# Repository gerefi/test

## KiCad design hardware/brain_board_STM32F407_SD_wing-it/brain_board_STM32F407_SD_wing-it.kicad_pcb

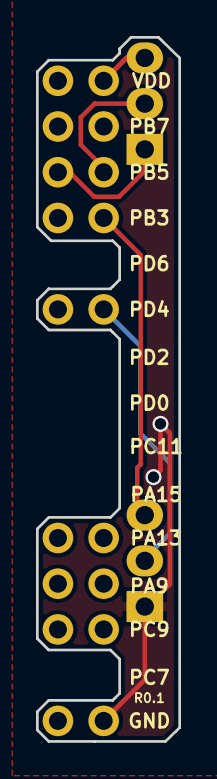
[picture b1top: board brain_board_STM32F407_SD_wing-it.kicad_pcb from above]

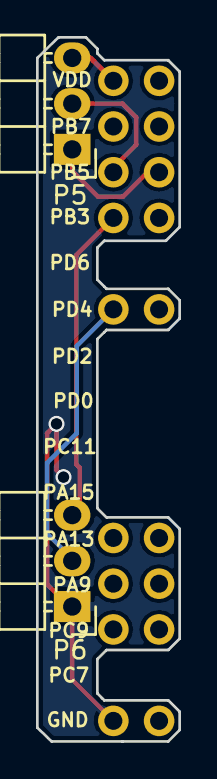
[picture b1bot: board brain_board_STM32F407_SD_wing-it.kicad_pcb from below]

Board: 2 copper layers, 7.9 x 39.1 mm, 8 parts (2 on the bottom side), 6 nets.

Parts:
P1: CONN_02X04; Pin_Header_Straight_2x04_Pitch2.54mm
P2: CONN_02X03; Pin_Header_Straight_2x03_Pitch2.54mm
P5, P6: CONN_01X03; Pin_Header_Angled_1x03
P7, P8, P11, P12: CONN_01X01; Pin_Header_Straight_1x01_Pitch2.54mm

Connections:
/PB3: P1.8, P6.3
/PB4: P1.5, P5.1
/PB5: P1.6, P5.2
/PD4: P6.2, P7.1
/VDD: P1.2, P5.3
GND: P6.1, P8.1

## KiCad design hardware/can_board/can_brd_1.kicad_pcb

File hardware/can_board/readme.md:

CAN using SN65HVD230

[Forum thread](http://gerefi.com/forum/viewtopic.php?f=4&t=353)

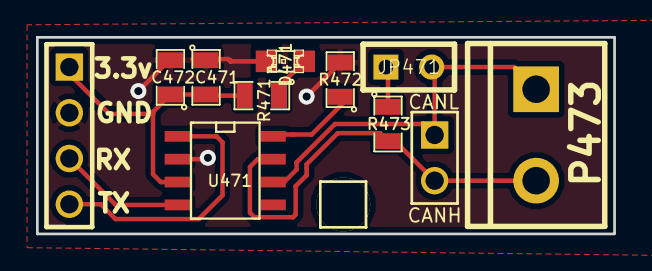
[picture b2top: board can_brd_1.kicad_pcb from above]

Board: 2 copper layers, 32.1 x 10.9 mm, 13 parts (1 on the bottom side), 9 nets.

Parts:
C471: .1uF; SM0805
C472: 4.7uF; SM0805
D471: RED; LED-0805_A
G471: LOGO; LOGO_F
JP471: JUMPER; JUMPER-2
M471: CONN_1; PIN_ARRAY_1
P471: CONN_4; PIN_ARRAY_4x1
P472: CONN_2; PIN_ARRAY_2_A
P473: CONN_2; bornier2
R471: 1k; SM0805
R472: 10k; SM0805
R473: 120; SM0805
U471: SN65HVD230; SO8E

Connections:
/3.3V: C471.2, C472.1, P471.1, R471.2, U471.3
/CANH: P472.2, P473.2, R473.2, U471.7
/CANL: JP471.2, P472.1, P473.1, U471.6
/CAN_RX: P471.3, U471.4
/CAN_TX: P471.4, U471.1
GND: C471.1, C472.2, D471.2, P471.2, R472.2, U471.2
unnamed: D471.1, R471.1
unnamed: JP471.1, R473.1
unnamed: R472.1, U471.8

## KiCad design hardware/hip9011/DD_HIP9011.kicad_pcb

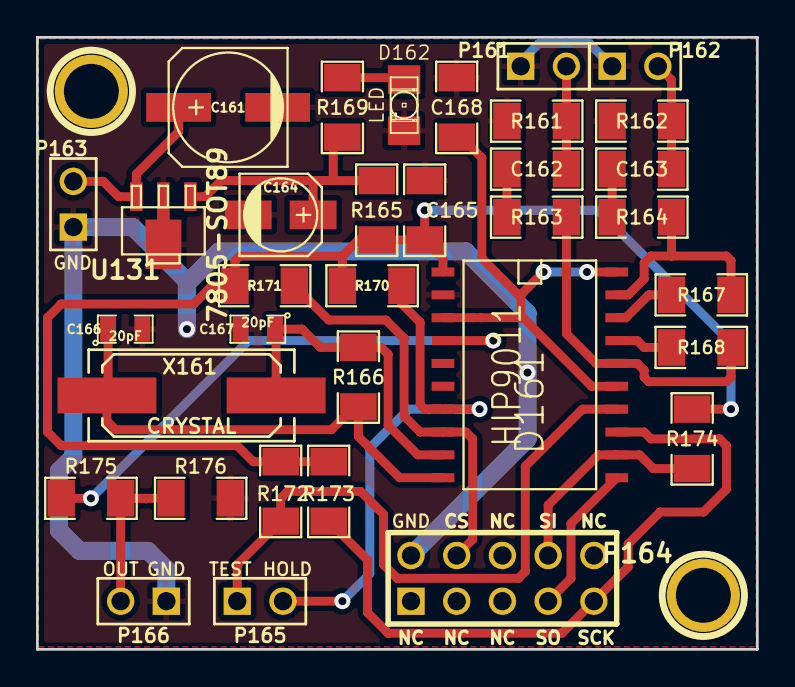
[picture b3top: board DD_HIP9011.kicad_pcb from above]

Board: 2 copper layers, 40.0 x 34.0 mm, 35 parts (1 on the bottom side), 24 nets.

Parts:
C161: 100u; c_elec_6.3x5.3
C162, C163: 47n; SM1206
C164: 10u; c_elec_4x5.3
C165: 100n; SM1206
C166, C167: 20pF; SM0805
C168: 22n; SM1206
D161: HIP9011; SO20L
D162: LED; LED-1206
G161: LOGO; LOGO_F
P161: KNOCK 1; PIN_ARRAY_2X1
P162: KNOCK 2; PIN_ARRAY_2X1
P163: 12V; PIN_ARRAY_2X1
P164: CONN_5X2; PIN_ARRAY_5x2
P165, P166: CONN_2; PIN_ARRAY_2X1
R161, R162, R166: 1M; SM1206
R163, R164, R175, R176: 10k; SM1206
R165: 10R; SM1206
R167, R168: 68k; SM1206
R169: 470R; SM1206
R170, R171, R172, R173, R174: 1K; SM1206
U131: 7805-SOT89; sot89
X161: CRYSTAL; Q_49U3HMS

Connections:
/5V: C165.1, D161.1, R165.2, R170.1, R171.1, R172.1, R173.1, R174.1
/+12V: C161.1, P163.2, U131.3
/CS: D161.8, P164.4, R171.2
/GND: C161.2, C164.2, C165.2, C166.2, C167.2, C168.2, D161.2, D162.2, P161.1, P162.1, P163.1, P164.2, P166.1, R161.2, R162.2, R176.2, U131.2
/INT/HLD: D161.7, P165.2, R170.2
/INTOUT: D161.4, R175.1
/KNOCK1: C162.1, P161.2, R161.1
/KNOCK2: C163.1, P162.2, R162.1
/OUT: P166.2, R175.2, R176.1
/SCK: D161.13, P164.9, R173.2
/SI: D161.12, P164.8, R174.2
/SO: D161.11, P164.7
/TEST: D161.14, P165.1, R172.2
unnamed: D162.1, R169.1
unnamed: C164.1, R165.1, R169.2, U131.1
unnamed: C167.1, D161.9, R166.2, X161.1
unnamed: C166.1, D161.10, R166.1, X161.2
unnamed: C163.2, R164.1
unnamed: C168.1, D161.3, D161.15, D161.20
unnamed: D161.16, R163.2, R168.2
unnamed: D161.17, R168.1
unnamed: D161.18, R167.1
unnamed: D161.19, R164.2, R167.2
unnamed: C162.2, R163.1

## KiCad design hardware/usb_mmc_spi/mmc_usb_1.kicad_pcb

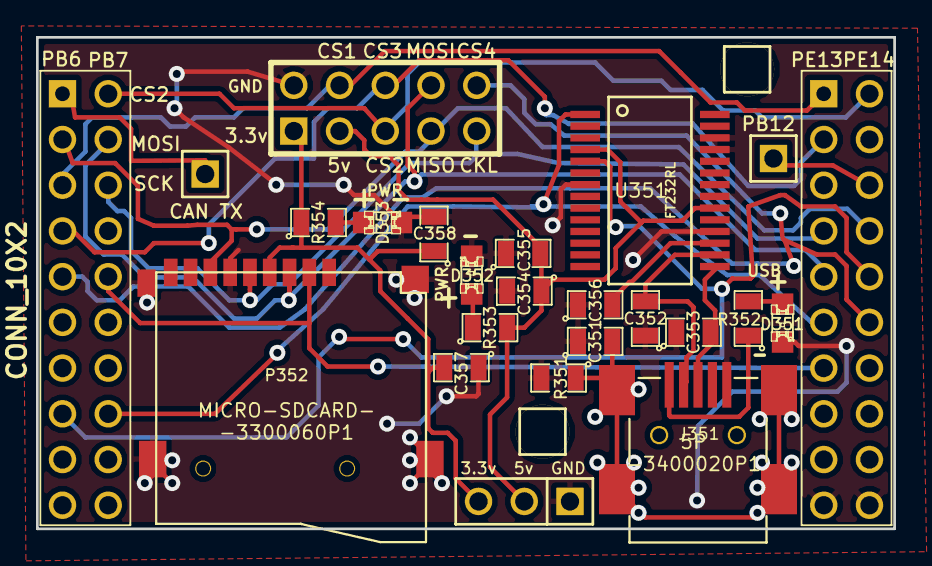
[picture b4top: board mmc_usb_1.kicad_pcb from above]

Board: 2 copper layers, 47.6 x 27.3 mm, 27 parts (1 on the bottom side), 23 nets.

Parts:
C351: 4700pF; SM0805
C352, C353: 47pF; SM0805
C354, C358: 4.7uF; SM0805
C355, C356, C357: .1uF; SM0805
D351: GREEN; LED-0805_A
D352, D353: RED; LED-0805_A
G305: LOGO; LOGO_F
J351: MINI-USB-5P-3400020P1
K351: CONN_3; PIN_ARRAY_3_A
M351, M352: CONN_1; PIN_ARRAY_1
P351: CONN_5X2; PIN_ARRAY_5x2_M
P352: MICRO-SDCARD-CONNECTOR-3300060P1
P353, P354: CONN_10X2; PIN_ARRAY_10X2_M
P355, P356: CONN_1; PIN_ARRAY_1
R351: 1M; SM0805
R352, R353, R354: 1k; SM0805
U351: FT232RL; ssop-28

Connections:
/3.3V: C357.2, C358.1, K351.3, P351.1, P352.4, R354.1
/5V: C354.1, C355.2, K351.2, P351.3, R353.2, U351.4, U351.20
/CAN_TX: P353.1, P356.1
/CS1: P351.4, P353.5, P354.1
/CS2: P351.5, P353.2, P354.2
/CS3: P351.6, P353.7, P354.3
/CS4: P351.10, P353.9, P354.12
/CS_SD_MODULE: P352.2, P353.10, P354.13
/D+: C353.2, J351.3, U351.15
/D-: C352.2, J351.2, U351.16
/SPI_MISO: P351.7, P352.7, P353.3, P354.8
/SPI_MOSI: P351.8, P352.3, P353.4, P354.9
/SPI_SCK: P351.9, P352.5, P353.6, P354.7
/USART_RX: P353.16, P354.11, U351.1
/USART_TX: P353.15, P354.10, U351.5
GND: C351.1, C352.1, C353.1, C354.2, C355.1, C356.1, C357.1, C358.2, D351.2, D352.2, D353.2, J351.5, K351.1, P351.2, P352.6, P352.G1, P352.G2, P352.G3, P352.G4, P354.19, P354.20, R351.2, U351.7, U351.18, U351.21, U351.25, U351.26
unnamed: J351.1, R352.1
unnamed: C351.2, J351.6, R351.1
unnamed: D351.1, R352.2
unnamed: D353.1, R354.2
unnamed: D352.1, R353.1
unnamed: P354.6, P355.1
unnamed: C356.2, U351.17
